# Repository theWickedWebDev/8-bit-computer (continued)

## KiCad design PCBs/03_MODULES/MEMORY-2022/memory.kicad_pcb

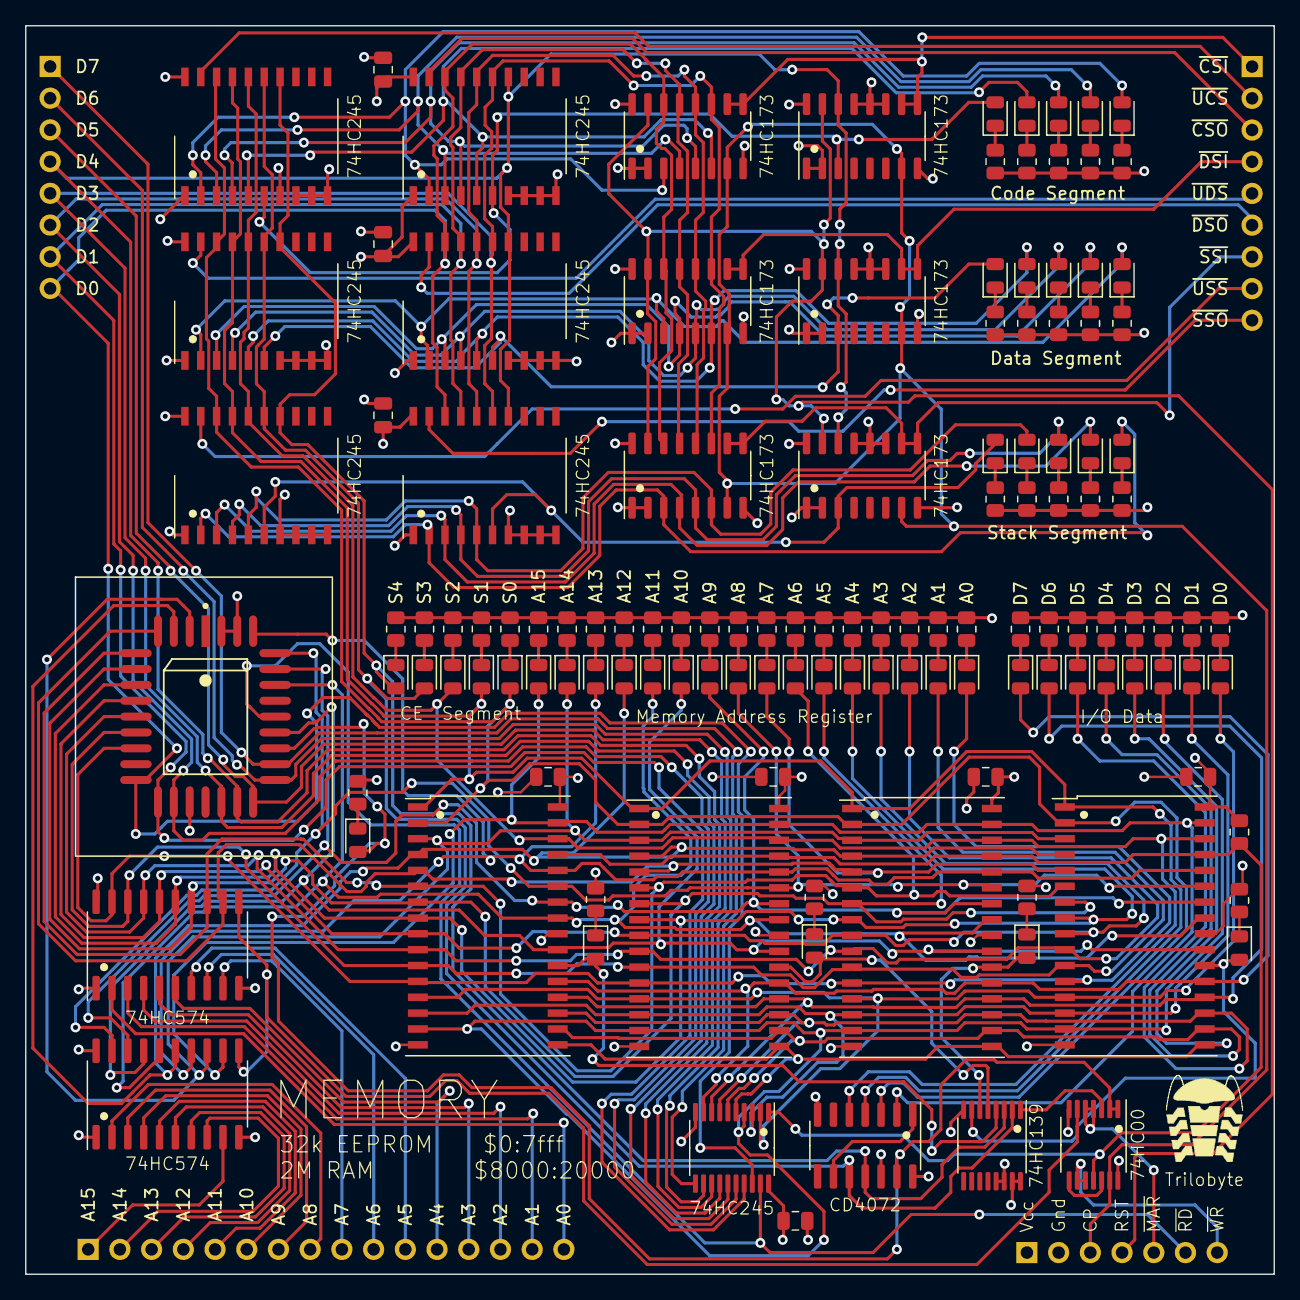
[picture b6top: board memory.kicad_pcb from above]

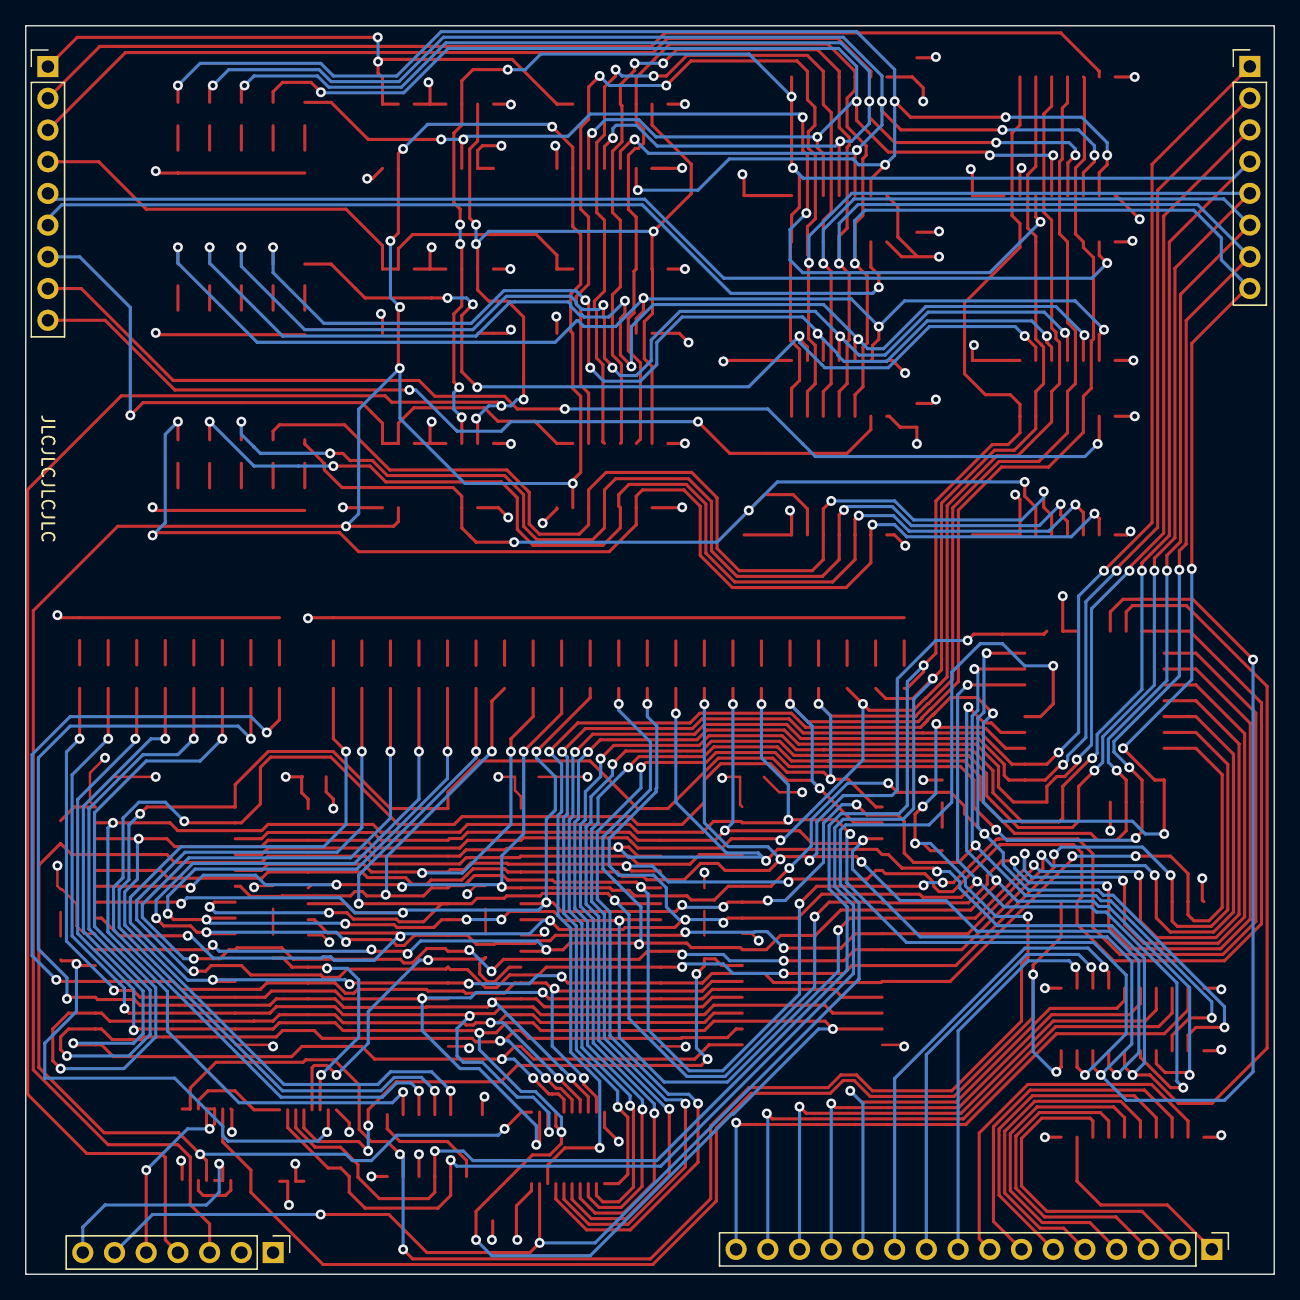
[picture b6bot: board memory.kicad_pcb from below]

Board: 4 copper layers, 100.0 x 100.0 mm, 134 parts (4 on the bottom side), 143 nets.

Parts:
C1, C2, C3, C4, C5, C6, C7, C8: C; C_0805_2012Metric
D1, D2, D3, D4, D5, D6, D7, D8, D9, D10, D11, D12, D13, D14, D15, D16, D17, D18, D19, D20, D21, D22, D23, D24, D25, D26, D27, D28, D29, D30, D31, D32, D33, D34, D35, D36, D37, D38, D39, D40, D41, D42, D43, D44, D45, D46, D47, D48, D49: LED; LED_0805_2012Metric
J1: Conn_01x07; PinHeader_1x07_P2.54mm_Vertical
J2: Conn_01x08; PinHeader_1x08_P2.54mm_Vertical
J3: Conn_01x16; PinHeader_1x16_P2.54mm_Vertical
J4: Conn_01x09; PinHeader_1x09_P2.54mm_Vertical
R1, R2, R3, R4, R5, R18, R19, R20, R21, R22, R23, R24, R25, R26, R27, R28, R29, R30, R31, R32, R33, R36, R37, R38, R39, R40, R41, R42, R43, R44, R45, R46, R47, R48, R49, R50: R_US; R_0805_2012Metric
R6, R7, R8, R9, R10, R11, R12, R13, R14, R15, R16, R17, R34, R35: R_Small_US; R_0805_2012Metric
U1: 74HC00; TSSOP-14_4.4x5mm_P0.65mm
U2: 4072; SO-14_3.9x8.65mm_P1.27mm
U3: 74HC139; TSSOP-16_4.4x5mm_P0.65mm
U4, U5, U6, U7: IS61C5128AS-25TLI; TSOP-II-32_21.0x10.2mm_P1.27mm
U8: 74HC245; TSSOP-20_4.4x6.5mm_P0.65mm
U9, U10: 74HC574; SO-20_5.3x12.6mm_P1.27mm
U11: PLCC32_28_28C256; PLCC-32-SOCKET-Microchip-32J-10_2001-B-IPC_A
U12, U13, U16, U17, U20, U21: 74HC173; SO-16_3.9x9.9mm_P1.27mm
U14, U15, U18, U19, U22, U23: 74HC245; SO-20_12.8x7.5mm_P1.27mm

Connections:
/ADDR0: D33.2 (A), U4.12 (A0), U5.12 (A0), U6.12 (A0), U7.12 (A0), U9.19 (Q0), U11.11 (A0)
/ADDR1: D32.2 (A), U4.11 (A1), U5.11 (A1), U6.11 (A1), U7.11 (A1), U9.18 (Q1), U11.10 (A1)
/ADDR2: D31.2 (A), U4.10 (A2), U5.10 (A2), U6.10 (A2), U7.10 (A2), U9.17 (Q2), U11.9 (A2)
/ADDR3: D30.2 (A), U4.9 (A3), U5.9 (A3), U6.9 (A3), U7.9 (A3), U9.16 (Q3), U11.8 (A3)
/ADDR4: D29.2 (A), U4.8 (A4), U5.8 (A4), U6.8 (A4), U7.8 (A4), U9.15 (Q4), U11.7 (A4)
/ADDR5: D28.2 (A), U4.7 (A5), U5.7 (A5), U6.7 (A5), U7.7 (A5), U9.14 (Q5), U11.6 (A5)
/ADDR6: D27.2 (A), U4.6 (A6), U5.6 (A6), U6.6 (A6), U7.6 (A6), U9.13 (Q6), U11.5 (A6)
/ADDR7: D26.2 (A), U4.5 (A7), U5.5 (A7), U6.5 (A7), U7.5 (A7), U9.12 (Q7), U11.4 (A7)
/ADDR8: D25.2 (A), U4.27 (A8), U5.27 (A8), U6.27 (A8), U7.27 (A8), U10.19 (Q0), U11.29 (A8)
/ADDR9: D24.2 (A), U4.26 (A9), U5.26 (A9), U6.26 (A9), U7.26 (A9), U10.18 (Q1), U11.28 (A9)
/ADDR10: D23.2 (A), U4.23 (A10), U5.23 (A10), U6.23 (A10), U7.23 (A10), U10.17 (Q2), U11.24 (A10)
/ADDR11: D22.2 (A), U4.25 (A11), U5.25 (A11), U6.25 (A11), U7.25 (A11), U10.16 (Q3), U11.27 (A11)
/ADDR12: D21.2 (A), U4.4 (A12), U5.4 (A12), U6.4 (A12), U7.4 (A12), U10.15 (Q4), U11.3 (A12)
/ADDR13: D20.2 (A), U4.28 (A13), U5.28 (A13), U6.28 (A13), U7.28 (A13), U10.14 (Q5), U11.30 (A13)
/ADDR14: D19.2 (A), U4.3 (A14), U5.3 (A14), U6.3 (A14), U7.3 (A14), U10.13 (Q6), U11.2 (A14)
/ADDR15: D18.2 (A), U2.2, U4.31 (A15), U5.31 (A15), U6.31 (A15), U7.31 (A15), U10.12 (Q7)
/Data Segments/Code Segment/S0: D44.2 (A), U16.3 (Q0), U18.2 (A0), U19.2 (A0)
/Data Segments/Code Segment/S1: D43.2 (A), U16.4 (Q1), U18.3 (A1), U19.3 (A1)
/Data Segments/Code Segment/S2: D42.2 (A), U16.5 (Q2), U18.4 (A2), U19.4 (A2)
/Data Segments/Code Segment/S3: D41.2 (A), U16.6 (Q3), U18.5 (A3), U19.5 (A3)
/Data Segments/Code Segment/S4: D40.2 (A), U17.3 (Q0), U18.6 (A4), U19.6 (A4)
/Data Segments/Data Segment/S0: D39.2 (A), U12.3 (Q0), U14.2 (A0), U15.2 (A0)
/Data Segments/Data Segment/S1: D38.2 (A), U12.4 (Q1), U14.3 (A1), U15.3 (A1)
/Data Segments/Data Segment/S2: D37.2 (A), U12.5 (Q2), U14.4 (A2), U15.4 (A2)
/Data Segments/Data Segment/S3: D36.2 (A), U12.6 (Q3), U14.5 (A3), U15.5 (A3)
/Data Segments/Data Segment/S4: D35.2 (A), U13.3 (Q0), U14.6 (A4), U15.6 (A4)
/Data Segments/Stack Segment/S0: D49.2 (A), U20.3 (Q0), U22.2 (A0), U23.2 (A0)
/Data Segments/Stack Segment/S1: D48.2 (A), U20.4 (Q1), U22.3 (A1), U23.3 (A1)
/Data Segments/Stack Segment/S2: D47.2 (A), U20.5 (Q2), U22.4 (A2), U23.4 (A2)
/Data Segments/Stack Segment/S3: D46.2 (A), U20.6 (Q3), U22.5 (A3), U23.5 (A3)
/Data Segments/Stack Segment/S4: D45.2 (A), U21.3 (Q0), U22.6 (A4), U23.6 (A4)
/RAM Array/D0: D13.2 (A), U4.13 (I/O0), U5.13 (I/O0), U6.13 (I/O0), U7.13 (I/O0), U8.2 (A0)
/RAM Array/D1: D12.2 (A), U4.14 (I/O1), U5.14 (I/O1), U6.14 (I/O1), U7.14 (I/O1), U8.3 (A1)
/RAM Array/D2: D11.2 (A), U4.15 (I/O2), U5.15 (I/O2), U6.15 (I/O2), U7.15 (I/O2), U8.4 (A2)
/RAM Array/D3: D10.2 (A), U4.17 (I/O3), U5.17 (I/O3), U6.17 (I/O3), U7.17 (I/O3), U8.5 (A3)
/RAM Array/D4: D9.2 (A), U4.18 (I/O4), U5.18 (I/O4), U6.18 (I/O4), U7.18 (I/O4), U8.6 (A4)
/RAM Array/D5: D8.2 (A), U4.19 (I/O5), U5.19 (I/O5), U6.19 (I/O5), U7.19 (I/O5), U8.7 (A5)
/RAM Array/D6: D7.2 (A), U4.20 (I/O6), U5.20 (I/O6), U6.20 (I/O6), U7.20 (I/O6), U8.8 (A6)
/RAM Array/D7: D6.2 (A), U4.21 (I/O7), U5.21 (I/O7), U6.21 (I/O7), U7.21 (I/O7), U8.9 (A7)
/~EEPROM_EN: D34.2 (A), U1.1, U1.2, U2.13, U11.23 (~CE)
A0: J3.16, U9.2 (D0)
A1: J3.15, U9.3 (D1)
A2: J3.14, U9.4 (D2)
A3: J3.13, U9.5 (D3)
A4: J3.12, U9.6 (D4)
A5: J3.11, U9.7 (D5)
A6: J3.10, U9.8 (D6)
A7: J3.9, U9.9 (D7)
A8: J3.8, U10.2 (D0)
A9: J3.7, U10.3 (D1)
A10: J3.6, U10.4 (D2)
A11: J3.5, U10.5 (D3)
A12: J3.4, U10.6 (D4)
A13: J3.3, U10.7 (D5)
A14: J3.2, U10.8 (D6)
A15: J3.1, U10.9 (D7)
BUS0: J2.8, U8.18 (B0), U11.13 (I/O0), U12.14 (D0), U15.18 (B0), U16.14 (D0), U19.18 (B0), U20.14 (D0), U23.18 (B0)
BUS1: J2.7, U8.17 (B1), U11.14 (I/O1), U12.13 (D1), U15.17 (B1), U16.13 (D1), U19.17 (B1), U20.13 (D1), U23.17 (B1)
BUS2: J2.6, U8.16 (B2), U11.15 (I/O2), U12.12 (D2), U15.16 (B2), U16.12 (D2), U19.16 (B2), U20.12 (D2), U23.16 (B2)
BUS3: J2.5, U8.15 (B3), U11.18 (I/O3), U12.11 (D3), U15.15 (B3), U16.11 (D3), U19.15 (B3), U20.11 (D3), U23.15 (B3)
BUS4: J2.4, U8.14 (B4), U11.19 (I/O4), U13.14 (D0), U15.14 (B4), U17.14 (D0), U19.14 (B4), U21.14 (D0), U23.14 (B4)
BUS5: J2.3, U8.13 (B5), U11.20 (I/O5)
BUS6: J2.2, U8.12 (B6), U11.21 (I/O6)
BUS7: J2.1, U8.11 (B7), U11.22 (I/O7)
CLOCK: J1.3, U1.13, U12.7 (Cp), U13.7 (Cp), U16.7 (Cp), U17.7 (Cp), U20.7 (Cp), U21.7 (Cp)
GND: C1.2, C2.2, C3.2, C4.2, C5.2, C6.2, C7.2, C8.2, J1.2, R1.1, R2.1, R3.1, R4.1, R5.1, R6.1, R7.1, R8.1, R9.1, R10.1, R11.1, R12.1, R13.1, R14.1, R15.1, R16.1, R17.1, R18.1, R19.1, R20.1, R21.1, R22.1, R23.1, R24.1, R25.1, R26.1, R27.1, R28.1, R29.1, R30.1, R31.1, R32.1, R33.1, R35.1, R36.1, R37.1, R38.1, R39.1, R40.1, R41.1, R42.1, R43.1, R44.1, R45.1, R46.1, R47.1, R48.1, R49.1, R50.1, U1.7 (GND), U2.7 (VSS), U2.12, U3.8 (GND), U3.13 (A1), U3.14 (A0), U4.16 (GND), U4.24 (~OE), U5.16 (GND), U5.24 (~OE), U6.16 (GND), U6.24 (~OE), U7.16 (GND), U7.24 (~OE), U8.10 (GND), U9.1 (OE), U9.10 (GND), U10.1 (OE), U10.10 (GND), U11.16 (Gnd), U12.1 (Oe1), U12.2 (Oe2), U12.8 (GND), U13.1 (Oe1), U13.2 (Oe2), U13.8 (GND), U13.11 (D3), U13.12 (D2), U13.13 (D1), U14.7 (A5), U14.8 (A6), U14.9 (A7), U14.10 (GND), U15.7 (A5), U15.8 (A6), U15.9 (A7), U15.10 (GND), U16.1 (Oe1), U16.2 (Oe2), U16.8 (GND), U17.1 (Oe1), U17.2 (Oe2), U17.8 (GND), U17.11 (D3), U17.12 (D2), U17.13 (D1), U18.7 (A5), U18.8 (A6), U18.9 (A7), U18.10 (GND), U19.7 (A5), U19.8 (A6), U19.9 (A7), U19.10 (GND), U20.1 (Oe1), U20.2 (Oe2), U20.8 (GND), U21.1 (Oe1), U21.2 (Oe2), U21.8 (GND), U21.11 (D3), U21.12 (D2), U21.13 (D1), U22.7 (A5), U22.8 (A6), U22.9 (A7), U22.10 (GND), U23.7 (A5), U23.8 (A6), U23.9 (A7), U23.10 (GND)
LATCH_MAR: U1.6, U9.11 (Cp), U10.11 (Cp)
unnamed: D1.1 (K), R1.2
unnamed: D2.1 (K), R2.2
unnamed: D3.1 (K), R3.2
unnamed: D4.1 (K), R4.2
unnamed: D5.1 (K), R5.2
unnamed: D6.1 (K), R6.2
unnamed: D7.1 (K), R7.2
unnamed: D8.1 (K), R8.2
unnamed: D9.1 (K), R9.2
unnamed: D10.1 (K), R10.2
unnamed: D11.1 (K), R11.2
unnamed: D12.1 (K), R12.2
unnamed: D13.1 (K), R13.2
unnamed: D14.1 (K), R14.2
unnamed: D15.1 (K), R15.2
unnamed: D16.1 (K), R16.2
unnamed: D17.1 (K), R17.2
unnamed: D18.1 (K), R18.2
unnamed: D19.1 (K), R19.2
unnamed: D20.1 (K), R20.2
unnamed: D21.1 (K), R21.2
unnamed: D22.1 (K), R22.2
unnamed: D23.1 (K), R23.2
unnamed: D24.1 (K), R24.2
unnamed: D25.1 (K), R25.2
unnamed: D26.1 (K), R26.2
unnamed: D27.1 (K), R27.2
unnamed: D28.1 (K), R28.2
unnamed: D29.1 (K), R29.2
unnamed: D30.1 (K), R30.2
unnamed: D31.1 (K), R31.2
unnamed: D32.1 (K), R32.2
unnamed: D33.1 (K), R33.2
unnamed: D34.1 (K), R35.2
unnamed: D35.1 (K), R36.2
unnamed: D36.1 (K), R37.2
unnamed: D37.1 (K), R38.2
unnamed: D38.1 (K), R39.2
unnamed: D39.1 (K), R40.2
unnamed: D40.1 (K), R41.2
unnamed: D41.1 (K), R42.2
unnamed: D42.1 (K), R43.2
unnamed: D43.1 (K), R44.2
unnamed: D44.1 (K), R45.2
unnamed: D45.1 (K), R46.2
unnamed: D46.1 (K), R47.2
unnamed: D47.1 (K), R48.2
unnamed: D48.1 (K), R49.2
unnamed: D49.1 (K), R50.2
unnamed: U1.3, U3.1 (E)
unnamed: U1.8, U1.12
unnamed: U2.1, U2.9
RESET: J1.4, U12.15 (Mr), U13.15 (Mr), U16.15 (Mr), U17.15 (Mr), U20.15 (Mr), U21.15 (Mr)
SEGMENT0: D5.2 (A), U2.3, U4.2 (A16), U5.2 (A16), U6.2 (A16), U7.2 (A16), U14.18 (B0), U18.18 (B0), U22.18 (B0)
SEGMENT1: D4.2 (A), U2.4, U4.1 (A17), U5.1 (A17), U6.1 (A17), U7.1 (A17), U14.17 (B1), U18.17 (B1), U22.17 (B1)
SEGMENT2: D3.2 (A), U2.5, U4.30 (A18), U5.30 (A18), U6.30 (A18), U7.30 (A18), U14.16 (B2), U18.16 (B2), U22.16 (B2)
SEGMENT3: D2.2 (A), U2.10, U3.2 (A0), U14.15 (B3), U18.15 (B3), U22.15 (B3)
SEGMENT4: D1.2 (A), U2.11, U3.3 (A1), U14.14 (B4), U18.14 (B4), U22.14 (B4)
VCC: C1.1, C2.1, C3.1, C4.1, C5.1, C6.1, C7.1, C8.1, J1.1, R34.2, U1.14 (VCC), U2.14 (VDD), U3.15 (E), U3.16 (VCC), U4.32 (VDD), U5.32 (VDD), U6.32 (VDD), U7.32 (VDD), U8.20 (VCC), U9.20 (VCC), U10.20 (VCC), U11.31 (~WE), U11.32 (Vcc), U12.16 (VCC), U13.16 (VCC), U14.1 (A->B), U14.20 (VCC), U15.1 (A->B), U15.20 (VCC), U16.16 (VCC), U17.16 (VCC), U18.1 (A->B), U18.20 (VCC), U19.1 (A->B), U19.20 (VCC), U20.16 (VCC), U21.16 (VCC), U22.1 (A->B), U22.20 (VCC), U23.1 (A->B), U23.20 (VCC)
~ASSERT_CODE_SEG: J4.3, U19.19 (CE)
~ASSERT_DATA_SEG: J4.6, U15.19 (CE)
~ASSERT_STACK_SEG: J4.9, U23.19 (CE)
~EN_CODE_SEG: J4.2, U18.19 (CE)
~EN_DATA_SEG: J4.5, U14.19 (CE)
~EN_STACK_SEG: J4.8, U22.19 (CE)
~LATCH_CODE_SEG: J4.1, U16.9 (E1), U16.10 (E2), U17.9 (E1), U17.10 (E2)
~LATCH_DATA_SEG: J4.4, U12.9 (E1), U12.10 (E2), U13.9 (E1), U13.10 (E2)
~LATCH_MAR: J1.5, U1.4, U1.5
~LATCH_STACK_SEG: J4.7, U20.9 (E1), U20.10 (E2), U21.9 (E1), U21.10 (E2)
~RAM_EN0: D17.2 (A), U3.4 (O0), U4.22 (~CE)
~RAM_EN1: D16.2 (A), U3.5 (O1), U5.22 (~CE)
~RAM_EN2: D15.2 (A), U3.6 (O2), U6.22 (~CE)
~RAM_EN3: D14.2 (A), U3.7 (O3), U7.22 (~CE)
~RAM_WRITE: R34.1, U1.11, U4.29 (~WE), U5.29 (~WE), U6.29 (~WE), U7.29 (~WE), U8.1 (A->B)
~READ: J1.6, U8.19 (CE), U11.25 (~OE)
~WRITE: J1.7, U1.9, U1.10

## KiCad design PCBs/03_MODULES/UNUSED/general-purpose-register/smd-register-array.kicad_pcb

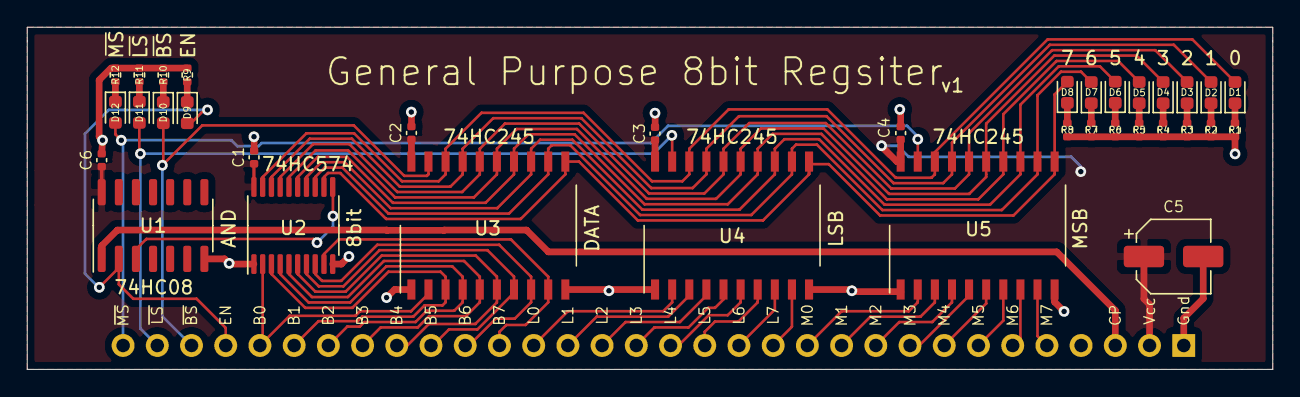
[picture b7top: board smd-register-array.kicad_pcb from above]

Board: 2 copper layers, 92.5 x 25.4 mm, 36 parts (1 on the bottom side), 52 nets.

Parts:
C1, C2, C3, C4, C6: CL05A106MQ5NUNC; C_0402_1005Metric
C5: SMD-ECAP-5x5.8; CP_Elec_5x5.8
D1, D2, D3, D4, D5, D6, D7, D8: 19-217/GHC-YR1S2/3T; LED_0603_1608Metric
D9, D10, D11, D12: 19-217/BHC-ZL1M2RY/3T; LED_0603_1608Metric
J1: Conn_01x32; PinHeader_1x32_P2.54mm_Vertical
R1, R2, R3, R4, R5, R6, R7, R8, R9, R10, R11, R12: 0402WGF1001TCE; R_0402_1005Metric
U1: 74HC08D,653; SOIC-14_3.9x8.7mm_P1.27mm
U2: 74HC574PW,118; TSSOP-20_4.4x6.5mm_P0.65mm
U3, U4, U5: 74HC245D,653; SO-20_12.8x7.5mm_P1.27mm

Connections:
/BUS_OUT: D10.2, J1.30, U3.19
/EN: D9.2, J1.29, U1.2
/LSB_OUT: D11.2, J1.31, U4.19
/MSB_OUT: D12.2, J1.32, U5.19
A0: D1.2, U2.19, U3.18, U4.18, U5.18
A1: D2.2, U2.18, U3.17, U4.17, U5.17
A2: D3.2, U2.17, U3.16, U4.16, U5.16
A3: D4.2, U2.16, U3.15, U4.15, U5.15
A4: D5.2, U2.15, U3.14, U4.14, U5.14
A5: D6.2, U2.14, U3.13, U4.13, U5.13
A6: D7.2, U2.13, U3.12, U4.12, U5.12
A7: D8.2, U2.12, U3.11, U4.11, U5.11
BUS_00: J1.28, U2.2, U3.2
BUS_01: J1.27, U2.3, U3.3
BUS_02: J1.26, U2.4, U3.4
BUS_03: J1.25, U2.5, U3.5
BUS_04: J1.24, U2.6, U3.6
BUS_05: J1.23, U2.7, U3.7
BUS_06: J1.22, U2.8, U3.8
BUS_07: J1.21, U2.9, U3.9
CLOCK: J1.3, U1.1
GND: C1.2, C2.2, C3.2, C4.2, C5.2, C6.2, J1.1, R1.2, R2.2, R3.2, R4.2, R5.2, R6.2, R7.2, R8.2, R9.2, R10.2, R11.2, R12.2, U1.7, U2.1, U2.10, U3.1, U3.10, U4.1, U4.10, U5.1, U5.10
LSB_00: J1.20, U4.2
LSB_01: J1.19, U4.3
LSB_02: J1.18, U4.4
LSB_03: J1.17, U4.5
LSB_04: J1.16, U4.6
LSB_05: J1.15, U4.7
LSB_06: J1.14, U4.8
LSB_07: J1.13, U4.9
MSB_00: J1.12, U5.2
MSB_01: J1.11, U5.3
MSB_02: J1.10, U5.4
MSB_03: J1.9, U5.5
MSB_04: J1.8, U5.6
MSB_05: J1.7, U5.7
MSB_06: J1.6, U5.8
MSB_07: J1.5, U5.9
unnamed: D1.1, R1.1
unnamed: D2.1, R2.1
unnamed: D3.1, R3.1
unnamed: D4.1, R4.1
unnamed: D5.1, R5.1
unnamed: D6.1, R6.1
unnamed: D7.1, R7.1
unnamed: D8.1, R8.1
unnamed: D9.1, R9.1
unnamed: D10.1, R10.1
unnamed: D11.1, R11.1
unnamed: D12.1, R12.1
unnamed: U1.3, U2.11
VCC: C1.1, C2.1, C3.1, C4.1, C5.1, C6.1, J1.2, U1.14, U2.20, U3.20, U4.20, U5.20

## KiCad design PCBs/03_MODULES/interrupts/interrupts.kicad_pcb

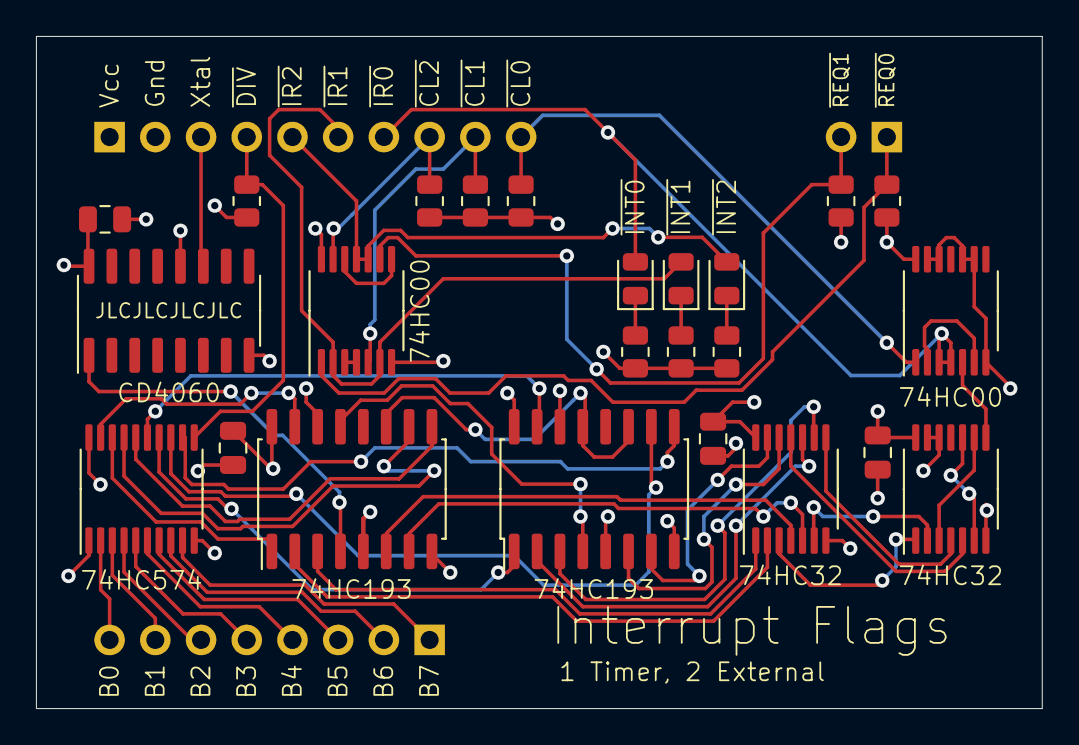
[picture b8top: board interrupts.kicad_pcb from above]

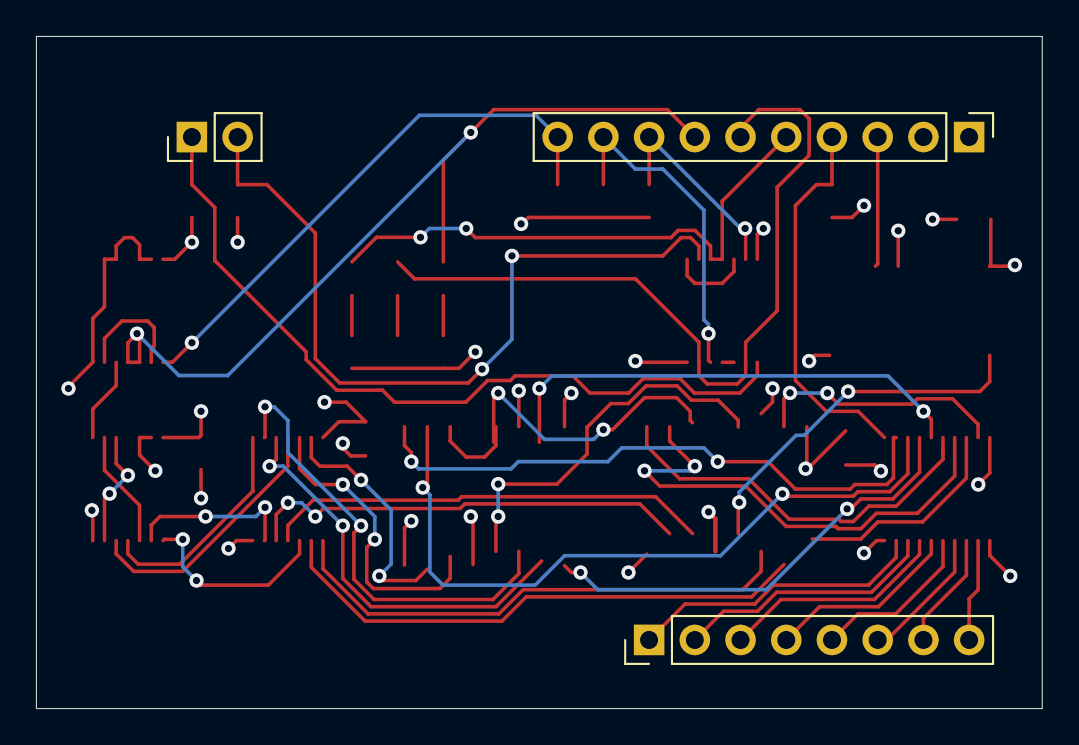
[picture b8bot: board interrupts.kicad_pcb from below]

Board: 4 copper layers, 55.9 x 37.3 mm, 27 parts (3 on the bottom side), 52 nets.

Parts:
C1, C2, C3, C4: C; C_0805_2012Metric
D1, D2, D3: LED; LED_0805_2012Metric
J1: Conn_01x10; PinHeader_1x10_P2.54mm_Vertical
J2: Conn_01x08; PinHeader_1x08_P2.54mm_Vertical
J3: Conn_01x02; PinHeader_1x02_P2.54mm_Vertical
R1, R2, R3, R4, R5, R6, R7, R8, R9: R_US; R_0805_2012Metric
U6: CD4060; SOIC-16_3.9x9.9mm_P1.27mm
U7: 74LS574; TSSOP-20_4.4x6.5mm_P0.65mm
U8, U9: 74LS193; SO-16_5.3x10.2mm_P1.27mm
U10, U11: 74LS32; TSSOP-14_4.4x5mm_P0.65mm
U12, U13: 74LS00; TSSOP-14_4.4x5mm_P0.65mm

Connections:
/BUS0: J2.8, U7.2
/BUS1: J2.7, U7.3
/BUS2: J2.6, U7.4
/BUS3: J2.5, U7.5
/BUS4: J2.4, U7.6
/BUS5: J2.3, U7.7
/BUS6: J2.2, U7.8
/BUS7: J2.1, U7.9
GND: C1.2, C2.2, C3.2, C4.2, J1.2, R1.2, R2.2, R3.2, U6.8, U6.12, U7.1, U7.10, U8.8, U8.14, U9.8, U9.14, U10.7, U11.7, U11.12, U11.13, U12.7, U12.9, U12.10, U12.12, U12.13, U13.7
unnamed: D1.1, R1.1
unnamed: D2.1, R2.1
unnamed: D3.1, R3.1
unnamed: U6.1, U8.4
unnamed: U7.12, U9.9
unnamed: U7.13, U9.10
unnamed: U7.14, U9.1
unnamed: U7.15, U9.15
unnamed: U7.16, U8.9
unnamed: U7.17, U8.10
unnamed: U7.18, U8.1
unnamed: U7.19, U8.15
unnamed: U8.11, U9.11, U9.13
unnamed: U8.13, U9.4
unnamed: U8.3, U10.1
unnamed: U8.2, U10.2
unnamed: U10.3, U11.1
unnamed: U8.6, U10.4
unnamed: U8.7, U10.5
unnamed: U10.6, U11.2
unnamed: U10.8, U11.4
unnamed: U9.3, U10.9
unnamed: U9.2, U10.10
unnamed: U10.11, U11.5
unnamed: U9.6, U10.12
unnamed: U9.7, U10.13
unnamed: U11.3, U11.9
unnamed: U11.8, U12.5
unnamed: U11.6, U11.10
unnamed: U12.2, U12.6
unnamed: U13.3, U13.4
unnamed: U13.8, U13.12
VCC: C1.1, C2.1, C3.1, C4.1, J1.1, R4.2, R5.2, R6.2, R7.2, R8.2, R9.2, U6.16, U7.20, U8.5, U8.16, U9.5, U9.16, U10.14, U11.14, U12.14, U13.14
XTAL: J1.3, U6.11
~INTCLR0: J1.10, R4.1, U12.1
~INTCLR1: J1.9, R5.1, U13.5
~INTCLR2: J1.8, R6.1, U13.13
~INTREQ0: D1.2, J1.7, U12.3, U12.4
~INTREQ1: D2.2, J1.6, U13.2, U13.6
~INTREQ2: D3.2, J1.5, U13.10, U13.11
~INT_REQ_0: J3.1, R7.1, U13.1
~INT_REQ_1: J3.2, R8.1, U13.9
~LATCH_TIMER_INTERRUPT_DIVISION: J1.4, R9.1, U7.11
